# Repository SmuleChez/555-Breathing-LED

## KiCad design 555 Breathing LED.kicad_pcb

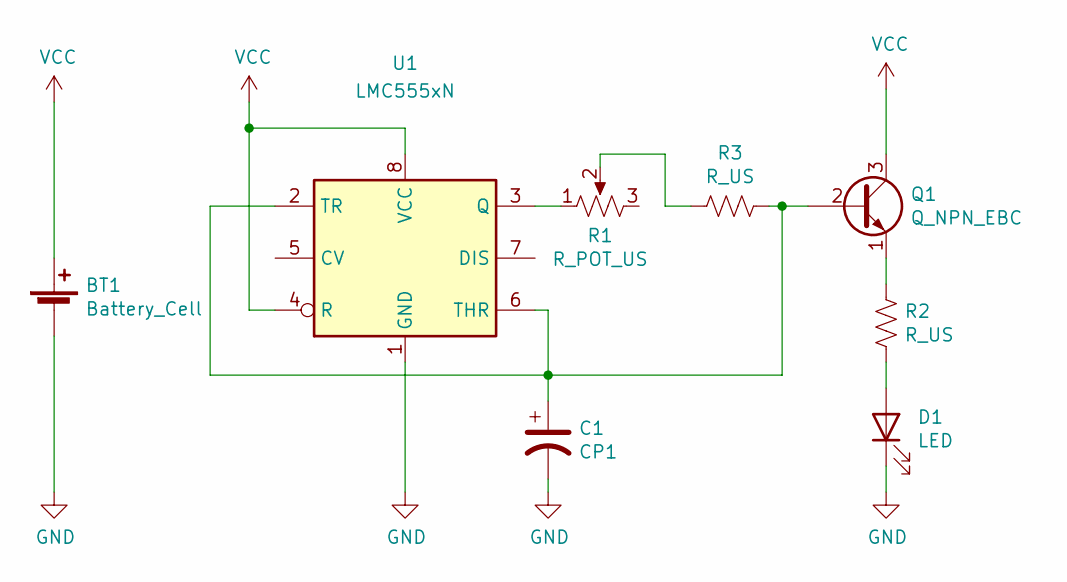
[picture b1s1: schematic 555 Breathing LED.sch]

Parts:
BT1: Battery_Cell; BatteryHolder_Keystone_107_1x23mm
C1: CP1; CP_Radial_D6.3mm_P2.50mm
D1: LED; LED_D10.0mm
Q1: Q_NPN_EBC; TO-92L_Wide
R1: R_POT_US; Potentiometer_Bourns_PTA2043_Single_Slide
R2, R3: R_US; R_Axial_DIN0309_L9.0mm_D3.2mm_P12.70mm_Horizontal
U1: LMC555xN; DIP-8_W7.62mm

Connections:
GND: BT1.2 (-), C1.2, D1.1 (K), U1.1 (GND)
unnamed: C1.1, Q1.2 (B), R3.1, U1.2 (TR), U1.6 (THR)
unnamed: D1.2 (A), R2.2
unnamed: Q1.1 (E), R2.1
unnamed: R1.1, U1.3 (Q)
unnamed: R1.2, R3.2
VCC: BT1.1 (+), Q1.3 (C), U1.4 (R), U1.8 (VCC)

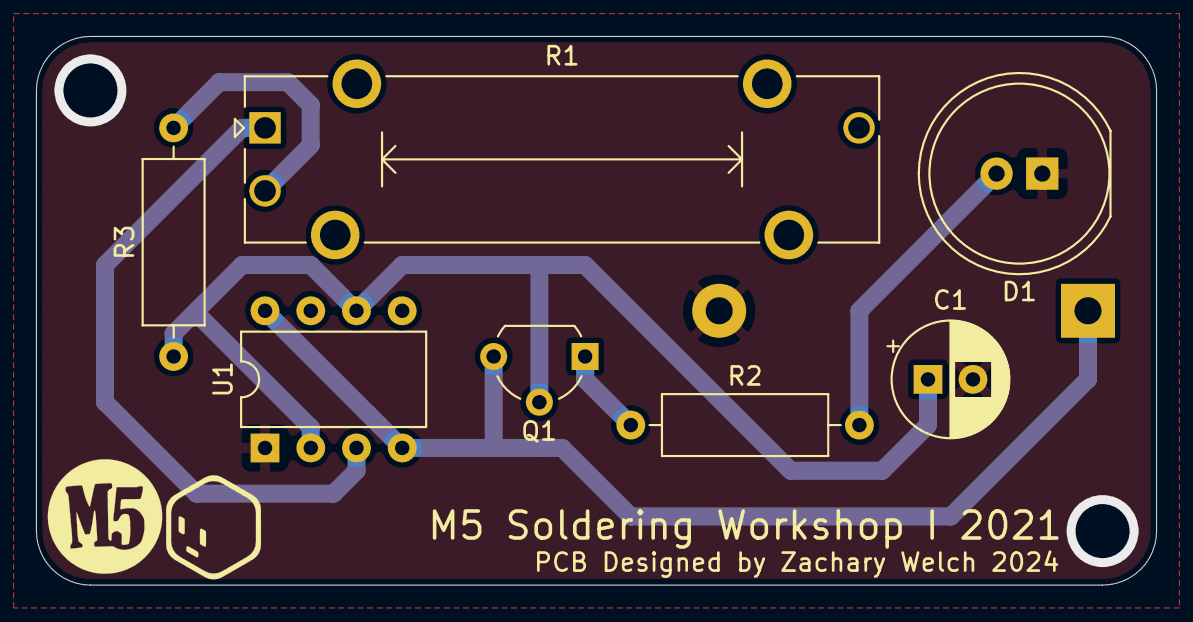
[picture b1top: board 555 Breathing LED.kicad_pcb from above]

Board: 2 copper layers, 62.2 x 30.5 mm, 8 parts (1 on the bottom side), 7 nets.

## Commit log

2021-09-10 initial commit
    initial commit
2021-09-11 Smaller Radius + m3 holes
2021-09-11 Fixed corners and m3 holes
2021-09-11 Updated Pcb and added graphics
2021-09-11 Updated PCB + Schematic
    Added battery holder
    Made PCB wider
    Moved ground plane to top layer
2021-09-11 Update 555 Breathing LED.kicad_pcb-bak
2021-09-11 Add exported gerber files
2021-09-11 Fixed BJT
